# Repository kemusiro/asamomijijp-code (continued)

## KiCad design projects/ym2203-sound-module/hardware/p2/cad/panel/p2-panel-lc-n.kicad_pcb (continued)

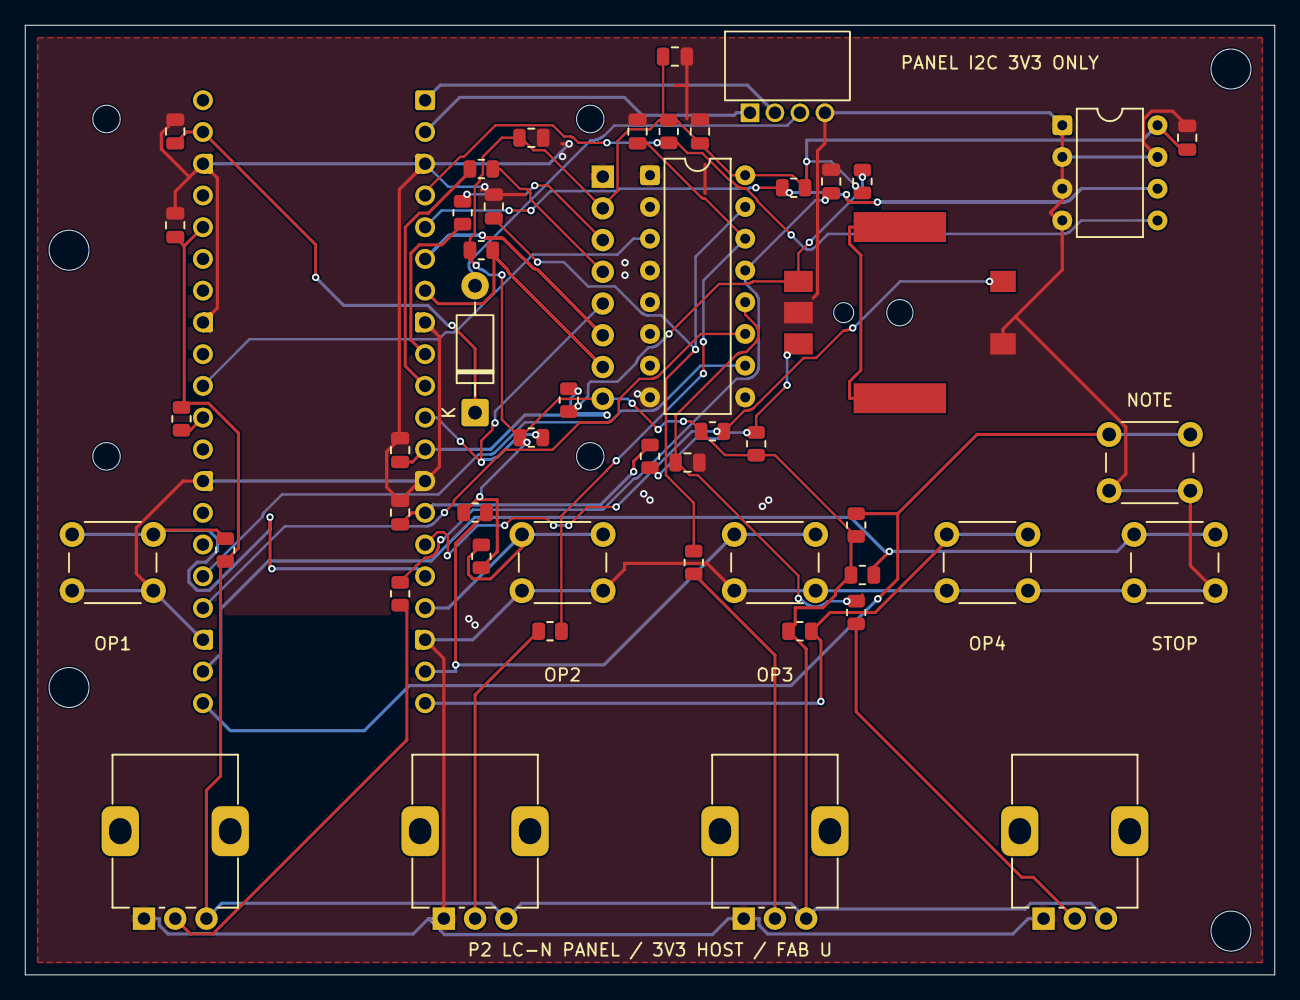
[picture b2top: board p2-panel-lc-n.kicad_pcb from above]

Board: 2 copper layers, 100.0 x 76.0 mm, 59 parts (1 on the bottom side), 38 nets.

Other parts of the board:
H1, H2, H3, H4: M3 support
H5, H6, H7, H8: M2 LCD 12mm

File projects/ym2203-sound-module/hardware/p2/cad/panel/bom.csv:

Reference,Value,Footprint,Sheet,Datasheet,Note
C1,1uF,Capacitor_SMD:C_0805_2012Metric,01-host-power,,
C2,100nF,Capacitor_SMD:C_0805_2012Metric,02-eeprom,,
C3,10uF,Capacitor_SMD:C_0805_2012Metric,01-host-power,,
C4,100nF,Capacitor_SMD:C_0805_2012Metric,01-host-power,,
U1,24FC256-I/P,Package_DIP:DIP-8_W7.62mm,02-eeprom,https://akizukidenshi.com/catalog/g/g103568/,"32KiB EEPROM,0x50;64byte pages; ACK polling <=10ms; explicit SAVE only; no extra pulls"
RV1,B10K RK09D117000B,Potentiometer_THT:Potentiometer_Alps_RK09K_Single_Vertical,03-pots,https://akizukidenshi.com/catalog/g/g114827/,center detent;6mm D shaft;S-42 16mm knob;RK09K vertical footprint electrical/mount pattern reference; collar/30mm shaft sample fit pending
R1,1k,Resistor_SMD:R_0805_2012Metric,03-pots,,
C5,100nF,Capacitor_SMD:C_0805_2012Metric,03-pots,,
RV2,B10K RK09D117000B,Potentiometer_THT:Potentiometer_Alps_RK09K_Single_Vertical,03-pots,https://akizukidenshi.com/catalog/g/g114827/,center detent;6mm D shaft;S-42 16mm knob;RK09K vertical footprint electrical/mount pattern reference; collar/30mm shaft sample fit pending
R2,1k,Resistor_SMD:R_0805_2012Metric,03-pots,,
C6,100nF,Capacitor_SMD:C_0805_2012Metric,03-pots,,
RV3,B10K RK09D117000B,Potentiometer_THT:Potentiometer_Alps_RK09K_Single_Vertical,03-pots,https://akizukidenshi.com/catalog/g/g114827/,center detent;6mm D shaft;S-42 16mm knob;RK09K vertical footprint electrical/mount pattern reference; collar/30mm shaft sample fit pending
R3,1k,Resistor_SMD:R_0805_2012Metric,03-pots,,
C7,100nF,Capacitor_SMD:C_0805_2012Metric,03-pots,,
RV4,B10K RK09D117000B,Potentiometer_THT:Potentiometer_Alps_RK09K_Single_Vertical,03-pots,https://akizukidenshi.com/catalog/g/g114827/,center detent;6mm D shaft;S-42 16mm knob;RK09K vertical footprint electrical/mount pattern reference; collar/30mm shaft sample fit pending
R4,1k,Resistor_SMD:R_0805_2012Metric,03-pots,,
C8,100nF,Capacitor_SMD:C_0805_2012Metric,03-pots,,
ENC1,ALPHA RE111F-4S1-152S4-15P-A,P2LC:RE111F_4S1_ReviewB,04-encoder,https://akizukidenshi.com/catalog/g/g114936/,30detents/15pulses;SMD;use supplied black shaft; ABC mapping/locator fit provisional; no 6mm knob
R5,2.7k,Resistor_SMD:R_0805_2012Metric,04-encoder,,
R6,1k,Resistor_SMD:R_0805_2012Metric,04-encoder,,
C9,10nF,Capacitor_SMD:C_0805_2012Metric,04-encoder,,
R7,2.7k,Resistor_SMD:R_0805_2012Metric,04-encoder,,
R8,1k,Resistor_SMD:R_0805_2012Metric,04-encoder,,
C10,10nF,Capacitor_SMD:C_0805_2012Metric,04-encoder,,
R9,4.7k,Resistor_SMD:R_0805_2012Metric,04-encoder,,
SW1,OP1 TVDP01-095BB1,Button_Switch_THT:SW_PUSH_6mm_H9.5mm,05-buttons,https://akizukidenshi.com/catalog/g/g117166/,6x6mm/9.5mm;4.5mm row pitch;duplicate pins;sample fit pending
R10,10k,Resistor_SMD:R_0805_2012Metric,05-buttons,,
SW2,OP2 TVDP01-095BB1,Button_Switch_THT:SW_PUSH_6mm_H9.5mm,05-buttons,https://akizukidenshi.com/catalog/g/g117166/,6x6mm/9.5mm;4.5mm row pitch;duplicate pins;sample fit pending
R11,10k,Resistor_SMD:R_0805_2012Metric,05-buttons,,
SW3,OP3 TVDP01-095BB1,Button_Switch_THT:SW_PUSH_6mm_H9.5mm,05-buttons,https://akizukidenshi.com/catalog/g/g117166/,6x6mm/9.5mm;4.5mm row pitch;duplicate pins;sample fit pending
R12,10k,Resistor_SMD:R_0805_2012Metric,05-buttons,,
SW4,OP4 TVDP01-095BB1,Button_Switch_THT:SW_PUSH_6mm_H9.5mm,05-buttons,https://akizukidenshi.com/catalog/g/g117166/,6x6mm/9.5mm;4.5mm row pitch;duplicate pins;sample fit pending
R13,10k,Resistor_SMD:R_0805_2012Metric,05-buttons,,
SW5,NOTE TVDP01-095BB1,Button_Switch_THT:SW_PUSH_6mm_H9.5mm,05-buttons,https://akizukidenshi.com/catalog/g/g117166/,6x6mm/9.5mm;4.5mm row pitch;duplicate pins;sample fit pending
R14,10k,Resistor_SMD:R_0805_2012Metric,05-buttons,,
SW6,STOP TVDP01-095BB1,Button_Switch_THT:SW_PUSH_6mm_H9.5mm,05-buttons,https://akizukidenshi.com/catalog/g/g117166/,6x6mm/9.5mm;4.5mm row pitch;duplicate pins;sample fit pending
R15,10k,Resistor_SMD:R_0805_2012Metric,05-buttons,,
R16,10k,Resistor_SMD:R_0805_2012Metric,06-lcd,,
R17,10k,Resistor_SMD:R_0805_2012Metric,06-lcd,,
R18,33,Resistor_SMD:R_0805_2012Metric,06-lcd,,
R19,33,Resistor_SMD:R_0805_2012Metric,06-lcd,,
J5,M154 LCD direct 1x8 socket / no harness,P2LC:LCD_M154_Socket_1x08,06-lcd,https://akizukidenshi.com/goodsaffix/M154-240240-RGB-8_20261020.pdf,"Top-view portrait pin1GND left. Rotate LCD90degCW: connector onright, pin1top. Replace factory right-angle header with straight downward male, mate to8.5mm socket+2.54mm header shoulder. 12mm supports conditional on measured11.04..12mm stack. Hole pitch38.72x27, not39.72. SPI/power order unchanged."
UPICO,Raspberry Pi Pico SC0915 RP2040,Module:RaspberryPi_Pico_Common_THT,01-panel-mcu,https://datasheets.raspberrypi.com/pico/pico-datasheet.pdf,"VSYS from3V3 Grove throughDPOWER. GPIO29VSYS/25LED/24VBUS/23SMPS internal,not externalADC. USB service only withGrove unplugged. Two20pin2.54mm sockets."
JUPLINK,110990037 Grove I2C 3V3 ONLY,P2LC:Grove_110990037_RA,01-panel-mcu,https://akizukidenshi.com/catalog/g/g112634/,150mm cable116938;no5V;power off for insertion;pin1SCL/2SDA/3VCC/4GND. Footprint deferred: RA drawing lacks unambiguous drill/top-view numbering;verify actual2mm part before PCB.
DPOWER,1N5819,Diode_THT:D_DO-41_SOD81_P10.16mm_Horizontal,01-panel-mcu,https://www.vishay.com/docs/88525/1n5817.pdf,"CommonSchottky reverseblock;USBserviceONLYGroveunplugged,avoidSDAbackfeed."
CPIN,10u X7R 10V,Capacitor_SMD:C_0805_2012Metric,01-panel-mcu,,
RPANELRUN,10k,Resistor_SMD:R_0805_2012Metric,01-panel-mcu,,
REEPSDA,4.7k,Resistor_SMD:R_0805_2012Metric,02-eeprom,,
REEPSCL,4.7k,Resistor_SMD:R_0805_2012Metric,02-eeprom,,
CMUX,100nF,Capacitor_SMD:C_0805_2012Metric,03-mux,,
UMUX,CD74HC4051E,Package_DIP:DIP-16_W7.62mm,03-mux,https://www.ti.com/lit/ds/symlink/cd74hc4051.pdf,HC2..6V;notHCT. CH0..3=knob1..4;C/INH/VEE=GND. 250ussettle then discardfirstADCsample;no audio goes throughthismux.

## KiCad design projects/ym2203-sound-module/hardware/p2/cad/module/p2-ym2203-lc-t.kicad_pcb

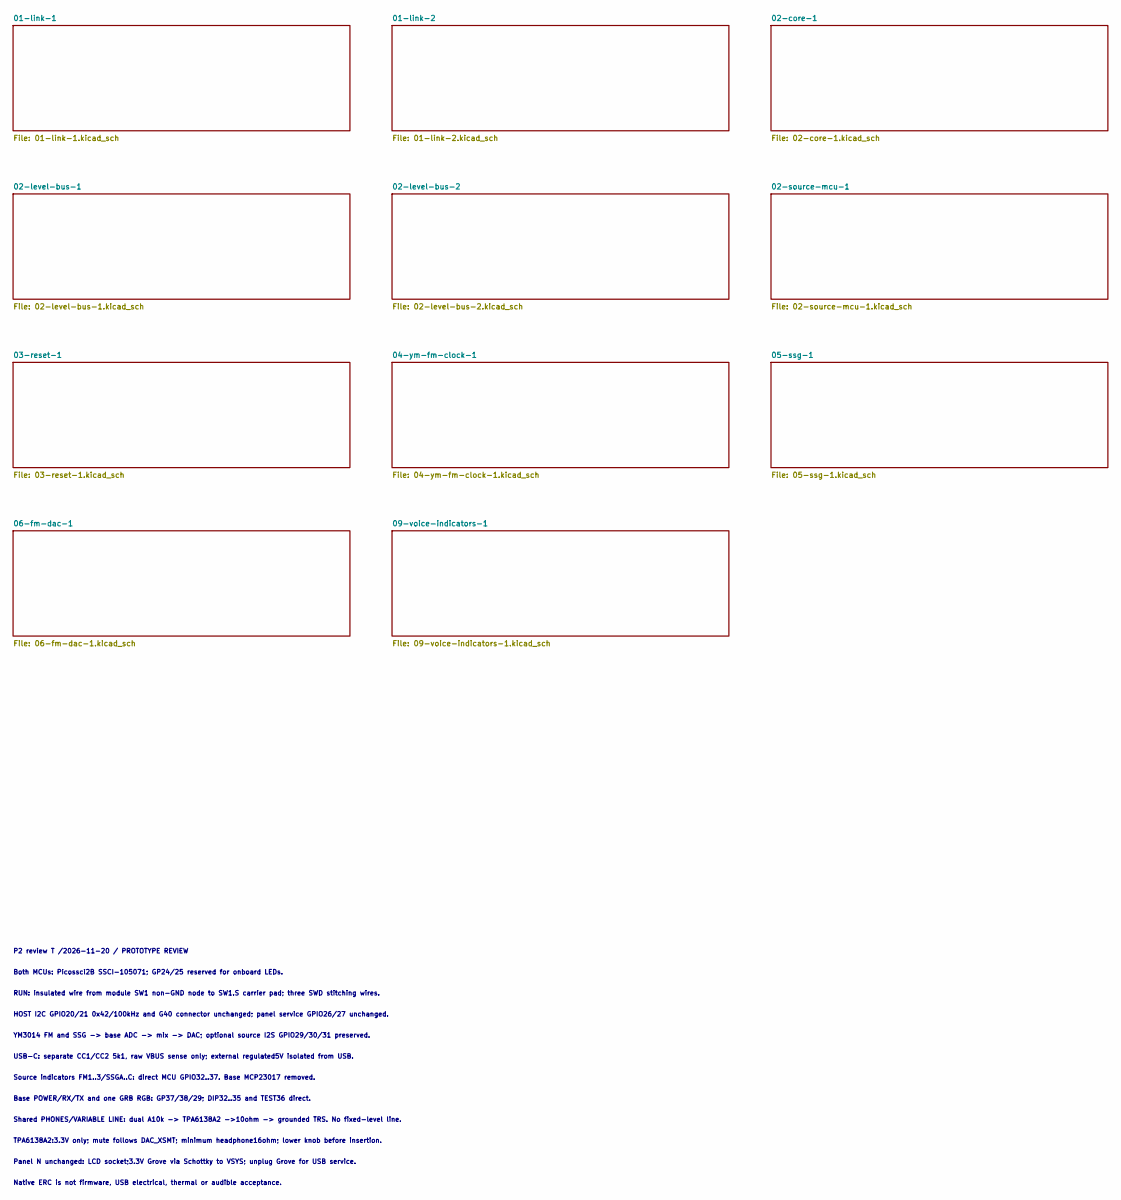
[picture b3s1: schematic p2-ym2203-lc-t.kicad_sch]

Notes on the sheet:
P2 review T /2026-11-20 / PROTOTYPE REVIEW
Both MCUs: Picossci2B SSCI-105071; GP24/25 reserved for onboard LEDs.
RUN: insulated wire from module SW1 non-GND node to SW1.S carrier pad; three SWD stitching wires.
HOST I2C GPIO20/21 0x42/100kHz and G40 connector unchanged; panel service GPIO26/27 unchanged.
YM3014 FM and SSG -> base ADC -> mix -> DAC; optional source I2S GPIO29/30/31 preserved.
USB-C: separate CC1/CC2 5k1, raw VBUS sense only; external regulated5V isolated from USB.
Source indicators FM1..3/SSGA..C: direct MCU GPIO32..37. Base MCP23017 removed.
Base POWER/RX/TX and one GRB RGB: GP37/38/29; DIP32..35 and TEST36 direct.
Shared PHONES/VARIABLE LINE: dual A10k -> TPA6138A2 ->10ohm -> grounded TRS. No fixed-level line.
TPA6138A2:3.3V only; mute follows DAC_XSMT; minimum headphone16ohm; lower knob before insertion.
Panel N unchanged: LCD socket;3.3V Grove via Schottky to VSYS; unplug Grove for USB service.
Native ERC is not firmware, USB electrical, thermal or audible acceptance.

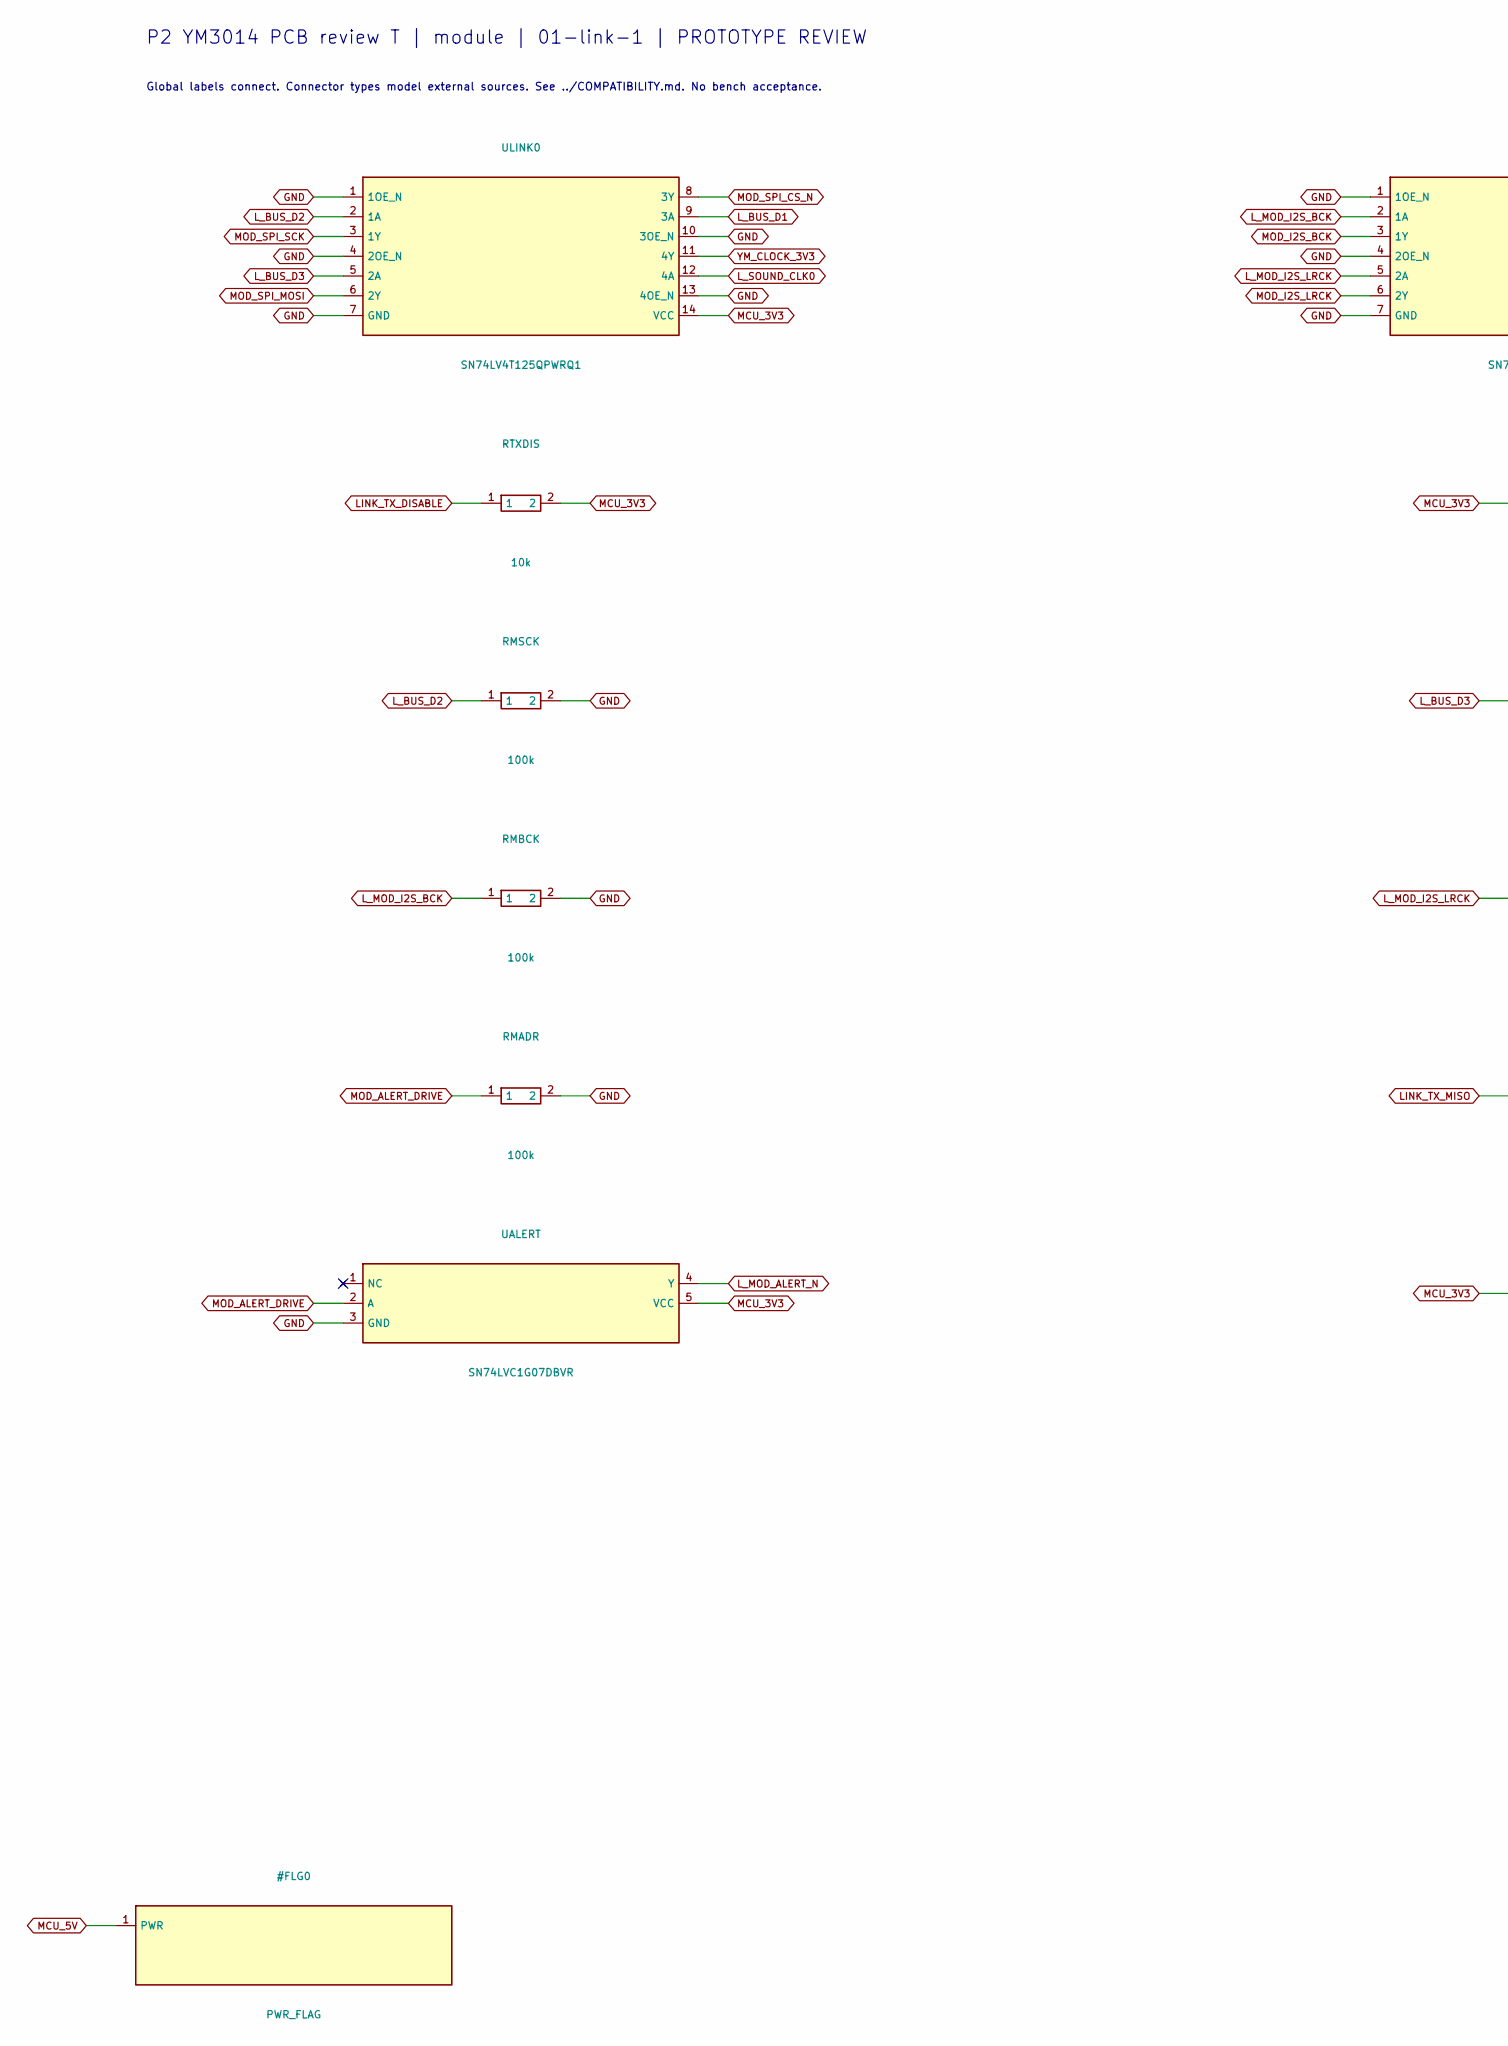
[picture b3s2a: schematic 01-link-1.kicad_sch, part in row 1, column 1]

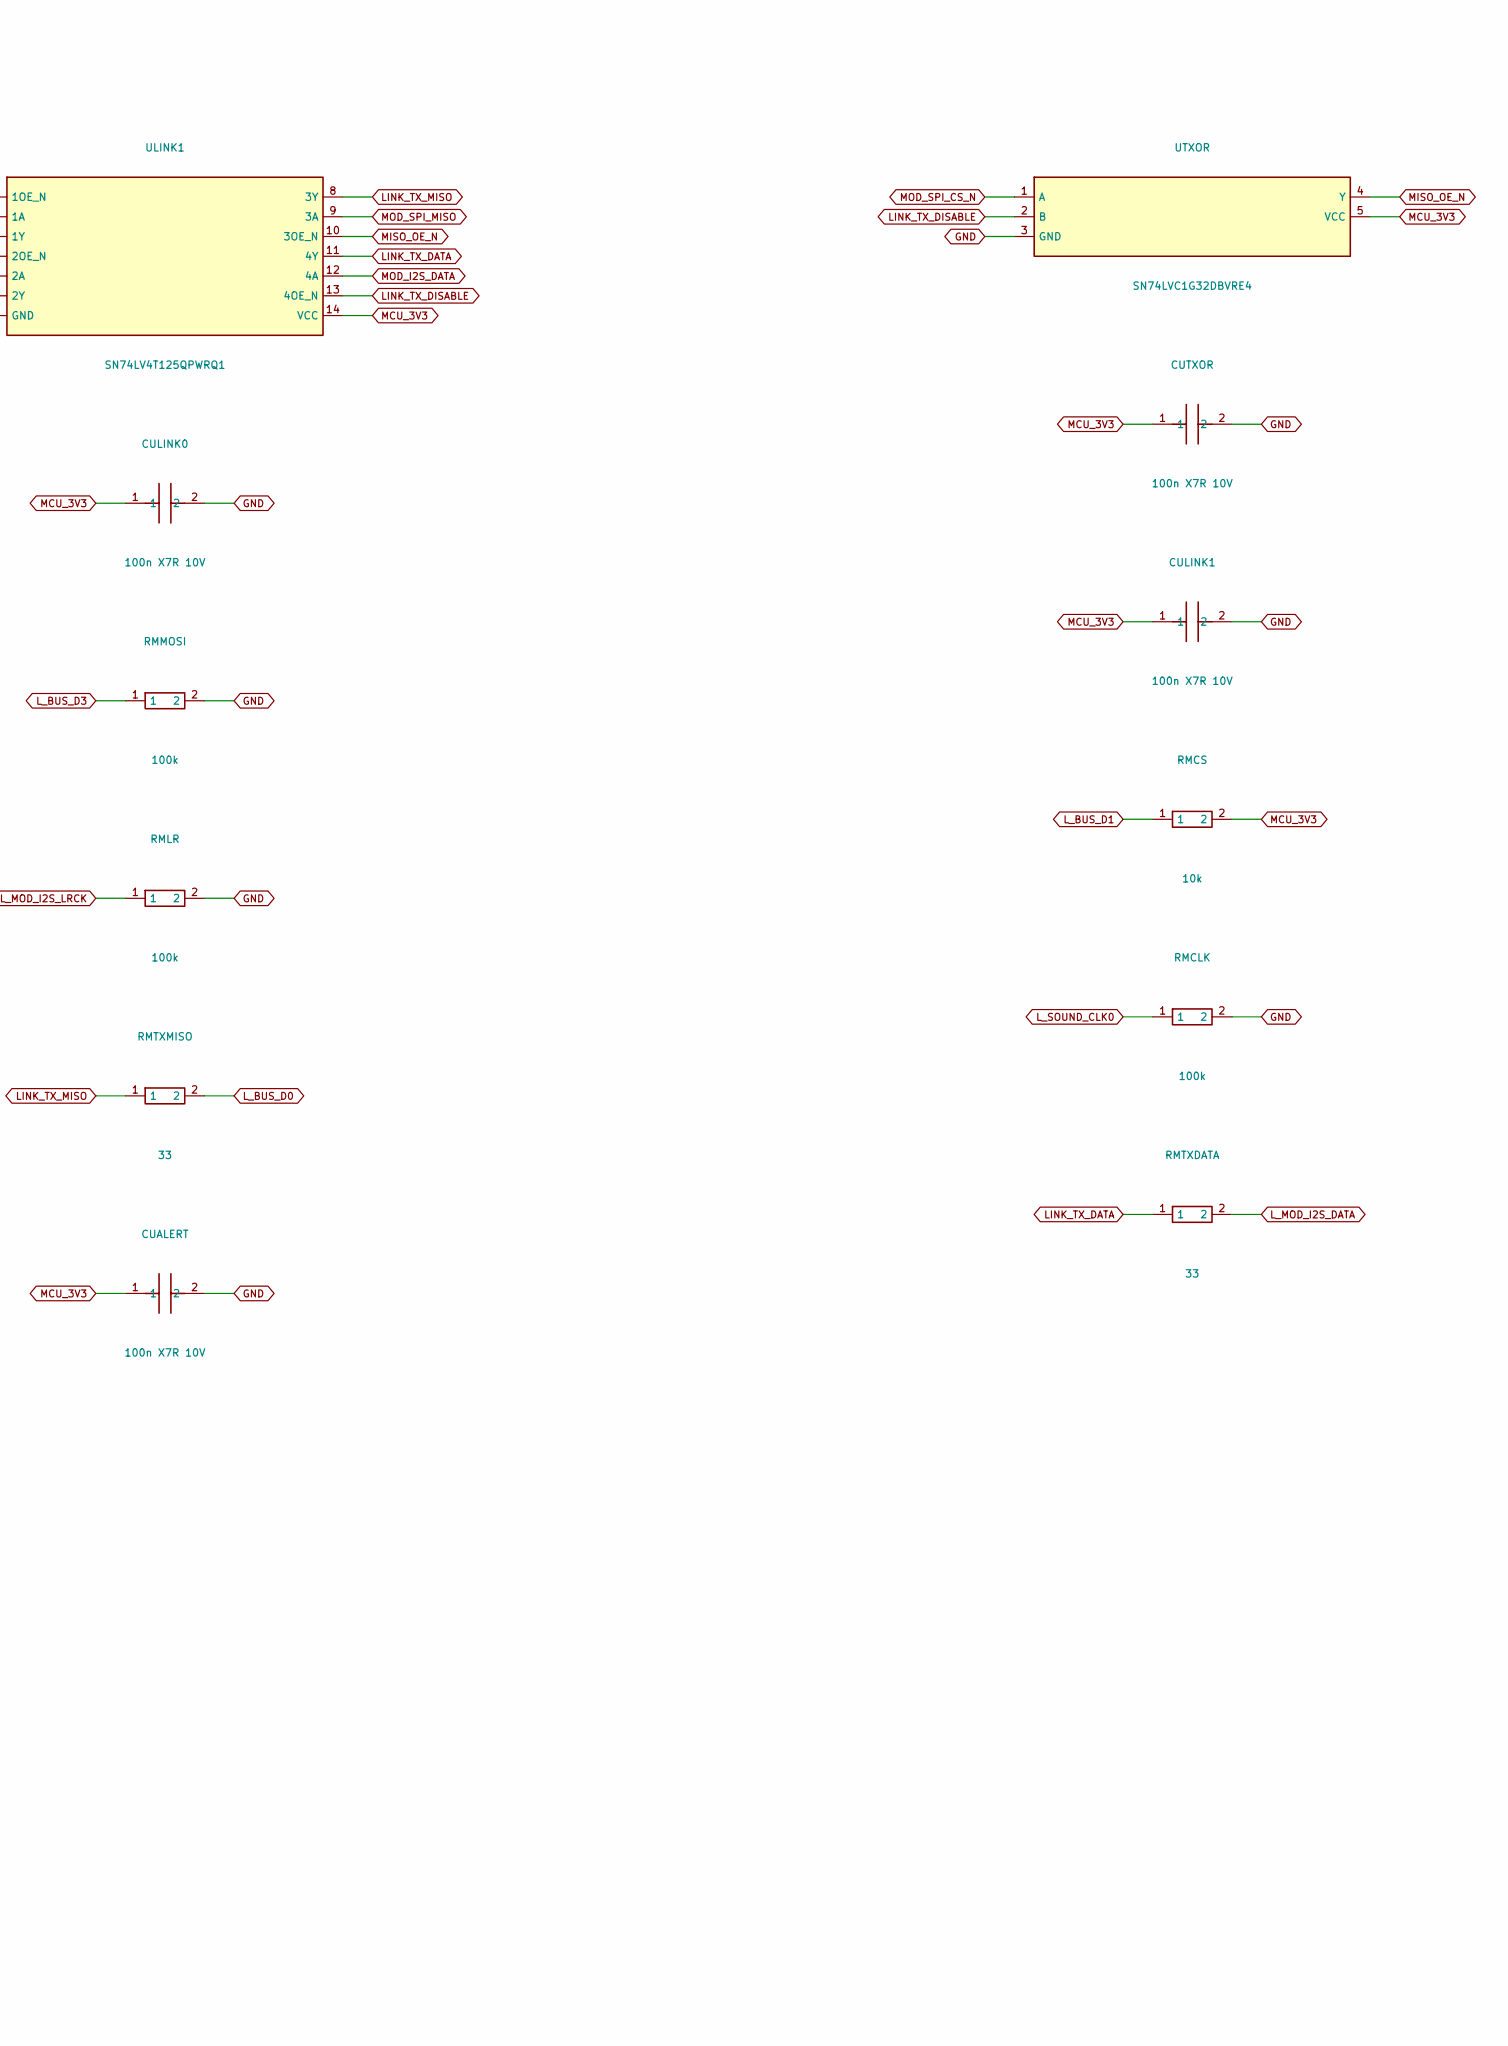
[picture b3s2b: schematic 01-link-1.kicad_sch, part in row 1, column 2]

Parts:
CUALERT: 100n X7R 10V; C_0805_2012Metric
CULINK0, CULINK1: 100n X7R 10V; C_0805_2012Metric
CUTXOR: 100n X7R 10V; C_0805_2012Metric
RMADR: 100k; R_0805_2012Metric
RMBCK: 100k; R_0805_2012Metric
RMCLK: 100k; R_0805_2012Metric
RMCS: 10k; R_0805_2012Metric
RMLR: 100k; R_0805_2012Metric
RMMOSI: 100k; R_0805_2012Metric
RMSCK: 100k; R_0805_2012Metric
RMTXDATA: 33; R_0805_2012Metric
RMTXMISO: 33; R_0805_2012Metric
RTXDIS: 10k; R_0805_2012Metric
UALERT: SN74LVC1G07DBVR; SOT-23-5
ULINK0, ULINK1: SN74LV4T125QPWRQ1; TSSOP-14_4.4x5mm_P0.65mm
UTXOR: SN74LVC1G32DBVRE4; SOT-23-5

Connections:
GND: CUALERT.2, CULINK0.2, CULINK1.2, CUTXOR.2, RMADR.2, RMBCK.2, RMCLK.2, RMLR.2, RMMOSI.2, RMSCK.2, UALERT.3 (GND), ULINK0.1 (1OE_N), ULINK0.4 (2OE_N), ULINK0.7 (GND), ULINK0.10 (3OE_N), ULINK0.13 (4OE_N), ULINK1.1 (1OE_N), ULINK1.4 (2OE_N), ULINK1.7 (GND), UTXOR.3 (GND); also elsewhere on the board
LINK_TX_DATA: RMTXDATA.1, ULINK1.11 (4Y)
LINK_TX_DISABLE: RTXDIS.1, ULINK1.13 (4OE_N), UTXOR.2 (B); also elsewhere on the board
LINK_TX_MISO: RMTXMISO.1, ULINK1.8 (3Y)
L_BUS_D0: RMTXMISO.2; also elsewhere on the board
L_BUS_D1: RMCS.1, ULINK0.9 (3A); also elsewhere on the board
L_BUS_D2: RMSCK.1, ULINK0.2 (1A); also elsewhere on the board
L_BUS_D3: RMMOSI.1, ULINK0.5 (2A); also elsewhere on the board
L_MOD_ALERT_N: UALERT.4 (Y); also elsewhere on the board
L_MOD_I2S_BCK: RMBCK.1, ULINK1.2 (1A); also elsewhere on the board
L_MOD_I2S_DATA: RMTXDATA.2; also elsewhere on the board
L_MOD_I2S_LRCK: RMLR.1, ULINK1.5 (2A); also elsewhere on the board
L_SOUND_CLK0: RMCLK.1, ULINK0.12 (4A); also elsewhere on the board
MCU_3V3: CUALERT.1, CULINK0.1, CULINK1.1, CUTXOR.1, RMCS.2, RTXDIS.2, UALERT.5 (VCC), ULINK0.14 (VCC), ULINK1.14 (VCC), UTXOR.5 (VCC); also elsewhere on the board
MISO_OE_N: ULINK1.10 (3OE_N), UTXOR.4 (Y)
MOD_ALERT_DRIVE: RMADR.1, UALERT.2 (A); also elsewhere on the board
MOD_I2S_BCK: ULINK1.3 (1Y); also elsewhere on the board
MOD_I2S_DATA: ULINK1.12 (4A); also elsewhere on the board
MOD_I2S_LRCK: ULINK1.6 (2Y); also elsewhere on the board
MOD_SPI_CS_N: ULINK0.8 (3Y), UTXOR.1 (A); also elsewhere on the board
MOD_SPI_MISO: ULINK1.9 (3A); also elsewhere on the board
MOD_SPI_MOSI: ULINK0.6 (2Y); also elsewhere on the board
MOD_SPI_SCK: ULINK0.3 (1Y); also elsewhere on the board
YM_CLOCK_3V3: ULINK0.11 (4Y); also elsewhere on the board

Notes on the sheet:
P2 YM3014 PCB review T | module | 01-link-1 | PROTOTYPE REVIEW
Global labels connect. Connector types model external sources. See ../COMPATIBILITY.md. No bench acceptance.

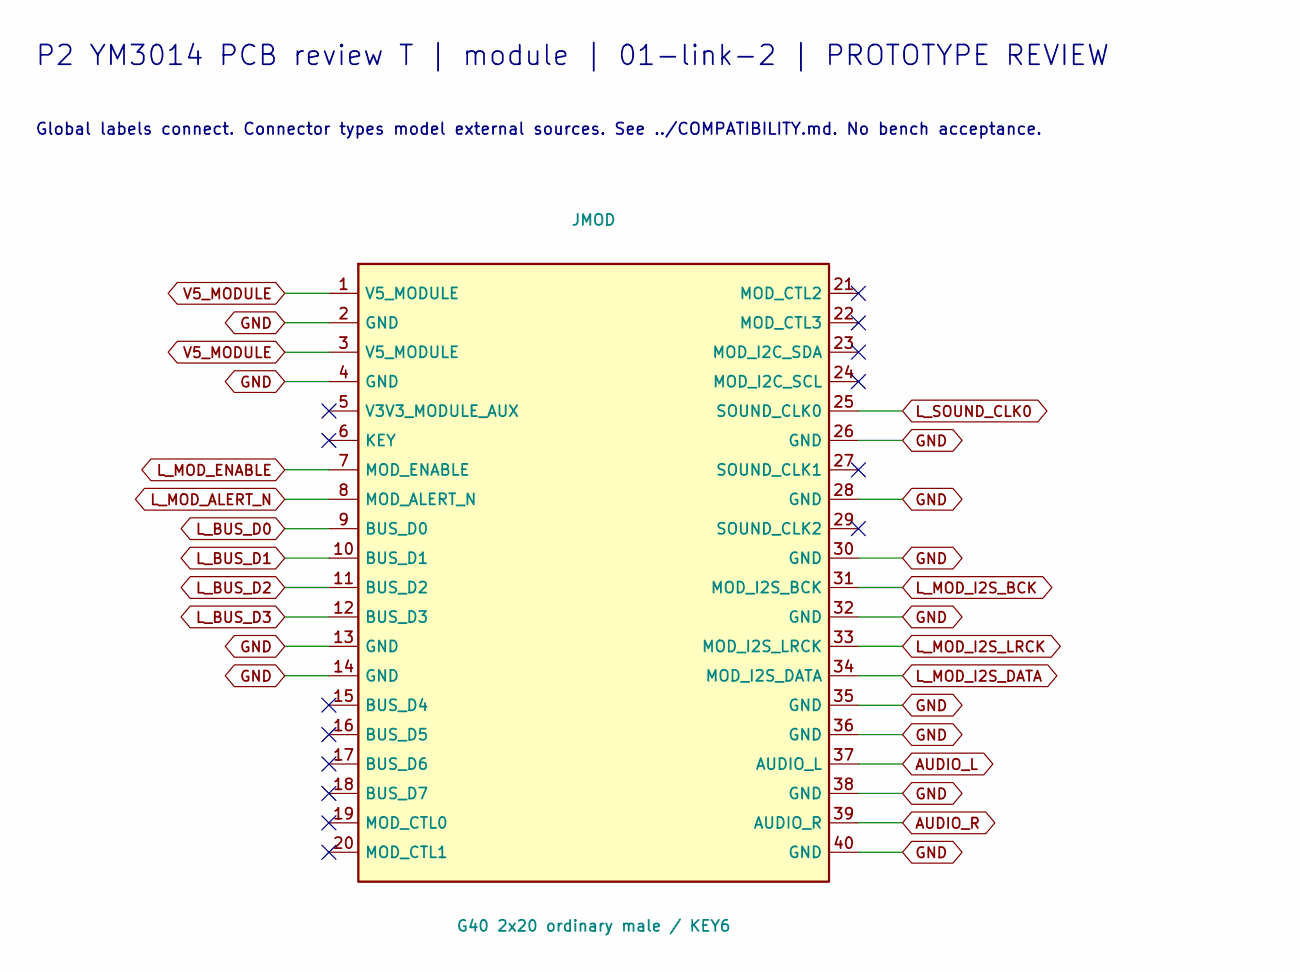
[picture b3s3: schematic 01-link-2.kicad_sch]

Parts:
JMOD: G40 2x20 ordinary male / KEY6; G40_Male_Underside

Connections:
AUDIO_L: JMOD.37 (AUDIO_L); also elsewhere on the board
AUDIO_R: JMOD.39 (AUDIO_R); also elsewhere on the board
GND: JMOD.2 (GND), JMOD.4 (GND), JMOD.13 (GND), JMOD.14 (GND), JMOD.26 (GND), JMOD.28 (GND), JMOD.30 (GND), JMOD.32 (GND), JMOD.35 (GND), JMOD.36 (GND), JMOD.38 (GND), JMOD.40 (GND); also elsewhere on the board
L_BUS_D0: JMOD.9 (BUS_D0); also elsewhere on the board
L_BUS_D1: JMOD.10 (BUS_D1); also elsewhere on the board
L_BUS_D2: JMOD.11 (BUS_D2); also elsewhere on the board
L_BUS_D3: JMOD.12 (BUS_D3); also elsewhere on the board
L_MOD_ALERT_N: JMOD.8 (MOD_ALERT_N); also elsewhere on the board
L_MOD_ENABLE: JMOD.7 (MOD_ENABLE); also elsewhere on the board
L_MOD_I2S_BCK: JMOD.31 (MOD_I2S_BCK); also elsewhere on the board
L_MOD_I2S_DATA: JMOD.34 (MOD_I2S_DATA); also elsewhere on the board
L_MOD_I2S_LRCK: JMOD.33 (MOD_I2S_LRCK); also elsewhere on the board
L_SOUND_CLK0: JMOD.25 (SOUND_CLK0); also elsewhere on the board
V5_MODULE: JMOD.1 (V5_MODULE), JMOD.3 (V5_MODULE); also elsewhere on the board

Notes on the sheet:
P2 YM3014 PCB review T | module | 01-link-2 | PROTOTYPE REVIEW
Global labels connect. Connector types model external sources. See ../COMPATIBILITY.md. No bench acceptance.

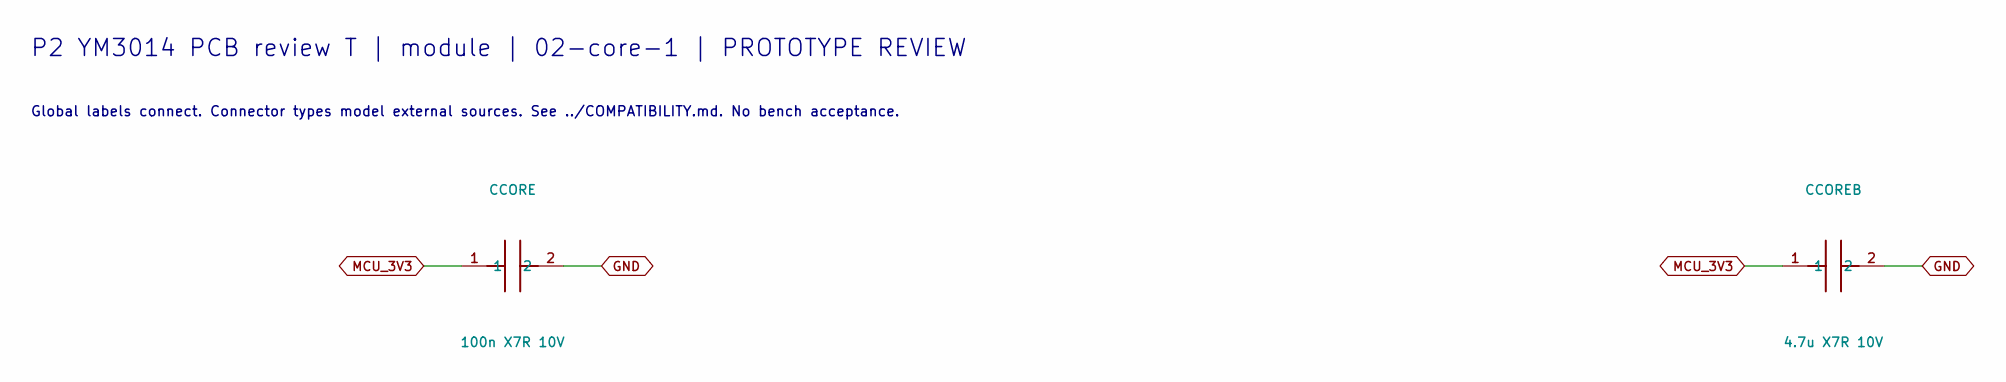
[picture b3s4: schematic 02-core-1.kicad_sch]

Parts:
CCORE: 100n X7R 10V; C_0805_2012Metric
CCOREB: 4.7u X7R 10V; C_0805_2012Metric

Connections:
GND: CCORE.2, CCOREB.2; also elsewhere on the board
MCU_3V3: CCORE.1, CCOREB.1; also elsewhere on the board

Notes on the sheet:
P2 YM3014 PCB review T | module | 02-core-1 | PROTOTYPE REVIEW
Global labels connect. Connector types model external sources. See ../COMPATIBILITY.md. No bench acceptance.
